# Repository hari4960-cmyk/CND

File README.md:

# HPA 2CH — MCU only ARTWORK review

- [Download KiCad schematic + routed PCB + outputs ZIP](HPA_2CH_MCU_ARTWORK_Review.zip)
- [Download Gerber + NC Drill review ZIP](HPA_2CH_MCU_Gerber_Review.zip)
- [Open KiCad project](HPA_2CH_MCU_ARTWORK/HPA_2CH.kicad_pro)
- [PCB top preview](HPA_2CH_MCU_ARTWORK/preview/PCB_top.png)
- [Schematic PDF](HPA_2CH_MCU_ARTWORK/preview/Schematic.pdf)
- [Read limitations and fabrication requirements](HPA_2CH_MCU_ARTWORK/README_KO.md)

MAX10 reserved area/interface removed; STM32 direct control. 200×160mm, 6 layers. KiCad 9.0.2 final checks: ERC 0, DRC 0, unrouted 0, schematic parity issues 0. **Engineering review only: RF matching, PA bias, hardware protection and thermal performance are unvalidated. External PA supplies/couplers required. Not a fabrication or power-up release.**

---

# HPA 2CH initial draft

- [Download all KiCad draft files](HPA_2CH_Initial_Draft.zip)
- [Open project source](HPA_2CH_DRAFT/HPA_2CH.kicad_pro)
- [Root schematic](HPA_2CH_DRAFT/HPA_2CH.kicad_sch)
- [PCB placement](HPA_2CH_DRAFT/HPA_2CH.kicad_pcb)
- [Schematic PDF](HPA_2CH_DRAFT/preview/HPA_2CH_Schematic.pdf)

**Initial placement draft, UNROUTED, not for fabrication or power-up.** FPGA device, integrated PA supplies and directional couplers are not implemented. RF matching/bias/thermal design is unverified. See the draft README and actual ERC/DRC results.

---

# STM32 LED10 PCB

## Latest: 100 × 100 mm — Rev.B

- [Complete 100mm design ZIP](STM32_LED10_100_RevB_Design_Review.zip): KiCad, BOM, firmware, schematic PDF, previews, verification reports and change history.
- [100mm Gerber and drill ZIP](STM32_LED10_100_RevB_Gerber_Drill_Review.zip).
- [100mm PCB artwork preview](STM32_LED10_100_RevB_PCB_top.png).

PCB resized from 200×200mm to 100×100mm through component relocation and fresh routing. Component pad/drill sizes, circuit connectivity and firmware behavior are unchanged. Two copper layers retained. ERC/DRC: zero violations, zero unconnected pads, zero schematic parity issues; 38 connectivity/geometry checks and 6 sequencer logic tests passed.

## Preserved: 200 × 200 mm — Rev.A

- [Original 200mm design ZIP](STM32_LED10_Design.zip).
- [Original 200mm Gerber and drill ZIP](STM32_LED10_Gerber.zip).

## Download

Open the desired ZIP on GitHub and select **Download raw file**, or use **Code → Download ZIP** for the whole repository. Use the files marked **100mm / Rev.B** for the latest size.

**Engineering review drafts; not approved for manufacture.** Official manufacturer PDF electrical/package/stability review remains pending; no physical prototype or hardware test has been performed. See the included README and reports before fabrication.

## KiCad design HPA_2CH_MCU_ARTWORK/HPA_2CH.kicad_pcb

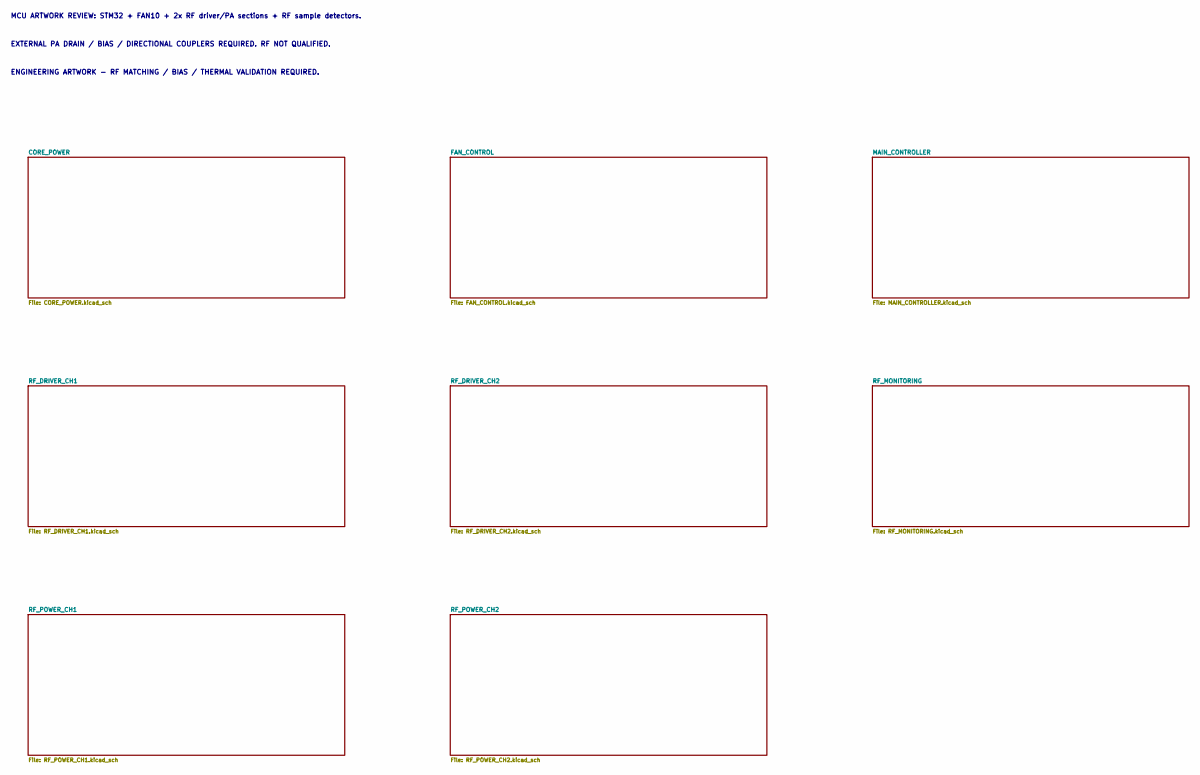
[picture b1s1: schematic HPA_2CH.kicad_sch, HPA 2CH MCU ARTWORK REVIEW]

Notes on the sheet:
MCU ARTWORK REVIEW: STM32 + FAN10 + 2x RF driver/PA sections + RF sample detectors.
EXTERNAL PA DRAIN / BIAS / DIRECTIONAL COUPLERS REQUIRED. RF NOT QUALIFIED.
ENGINEERING ARTWORK - RF MATCHING / BIAS / THERMAL VALIDATION REQUIRED.

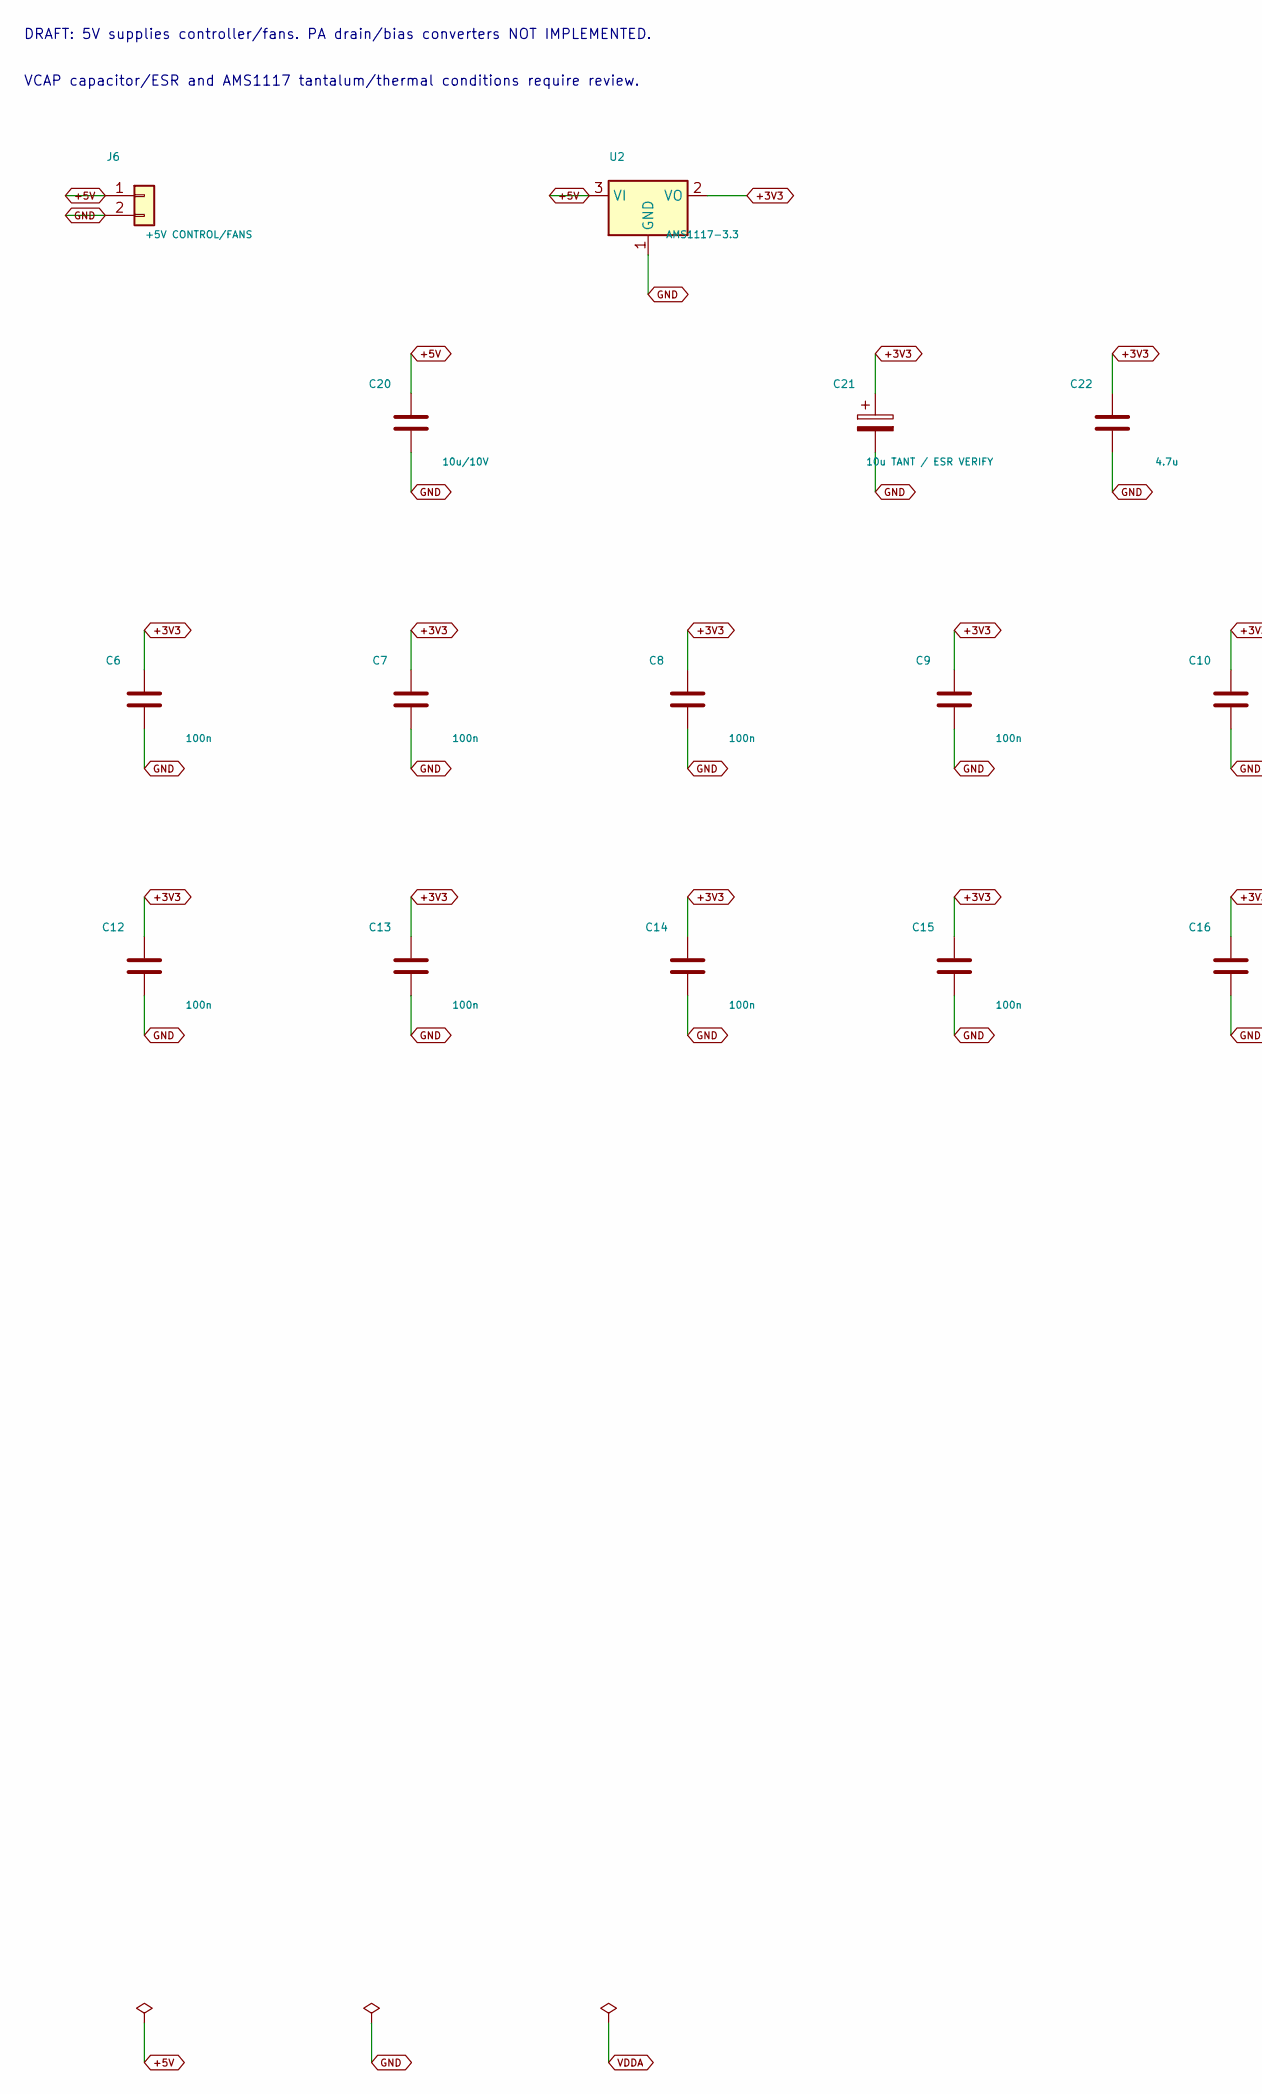
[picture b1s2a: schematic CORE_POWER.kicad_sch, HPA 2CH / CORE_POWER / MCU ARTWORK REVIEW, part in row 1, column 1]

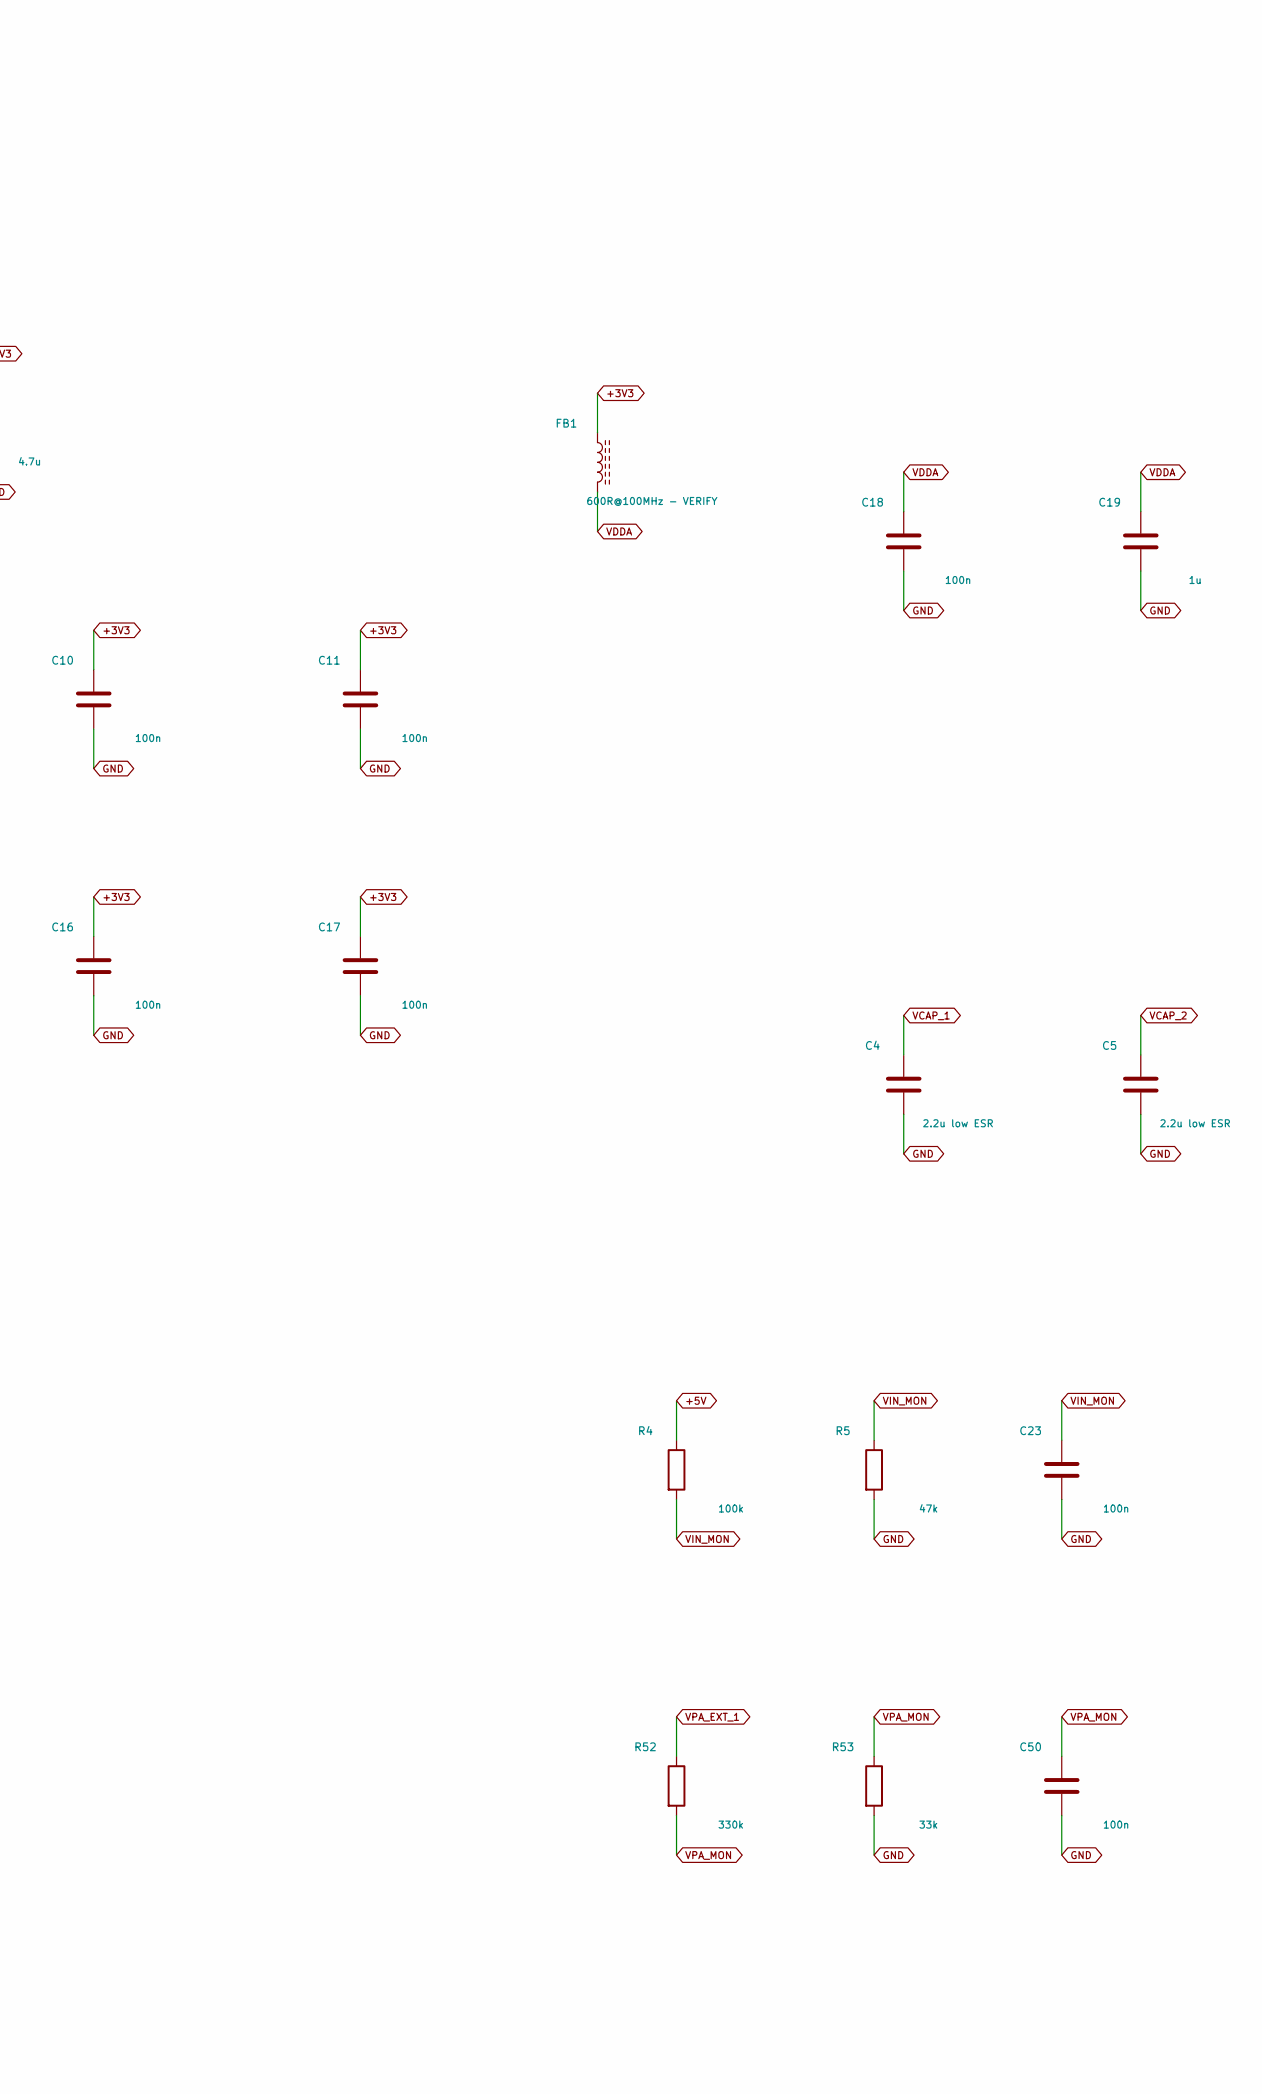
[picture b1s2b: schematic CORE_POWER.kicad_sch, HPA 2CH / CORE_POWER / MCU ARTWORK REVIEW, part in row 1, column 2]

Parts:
C4, C5: 2.2u low ESR; C_0603_1608Metric
C6, C7, C8, C9, C10, C11, C12, C13, C14, C15, C16, C17, C18, C23, C50: 100n; C_0603_1608Metric
C19: 1u; C_0603_1608Metric
C20: 10u/10V; C_0603_1608Metric
C21: 10u TANT / ESR VERIFY; CP_EIA-3216-18_Kemet-A
C22: 4.7u; C_0603_1608Metric
FB1: 600R@100MHz - VERIFY; R_0603_1608Metric
J6: +5V CONTROL/FANS; TerminalBlock_Phoenix_MKDS-1,5-2-5.08_1x02_P5.08mm_Horizont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
R4: 100k; R_0603_1608Metric
R5: 47k; R_0603_1608Metric
R52: 330k; R_0603_1608Metric
R53: 33k; R_0603_1608Metric
U2: AMS1117-3.3; SOT-223-3_TabPin2

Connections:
+3V3: C6.1, C7.1, C8.1, C9.1, C10.1, C11.1, C12.1, C13.1, C14.1, C15.1, C16.1, C17.1, C21.1, C22.1, FB1.1, U2.2 (VO); also elsewhere on the board
+5V: C20.1, J6.1, R4.1, U2.3 (VI); also elsewhere on the board
GND: C4.2, C5.2, C6.2, C7.2, C8.2, C9.2, C10.2, C11.2, C12.2, C13.2, C14.2, C15.2, C16.2, C17.2, C18.2, C19.2, C20.2, C21.2, C22.2, C23.2, C50.2, J6.2, R5.2, R53.2, U2.1 (GND); also elsewhere on the board
VCAP_1: C4.1; also elsewhere on the board
VCAP_2: C5.1; also elsewhere on the board
VDDA: C18.1, C19.1, FB1.2; also elsewhere on the board
VIN_MON: C23.1, R4.2, R5.1; also elsewhere on the board
VPA_EXT_1: R52.1; also elsewhere on the board
VPA_MON: C50.1, R52.2, R53.1; also elsewhere on the board

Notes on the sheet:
DRAFT: 5V supplies controller/fans. PA drain/bias converters NOT IMPLEMENTED.
VCAP capacitor/ESR and AMS1117 tantalum/thermal conditions require review.
